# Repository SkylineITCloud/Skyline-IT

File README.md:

# Skyline IT

The official single-page website for **Skyline IT**, a South African holding company building brands across technology, Internet Of Things (IoT), electronics, fashion, and education.

The site presents the Skyline IT story, its portfolio companies, core values, industry focus, and contact information.

## Live site structure

```text
Skyline IT/
├── index.html       # Complete responsive website: markup, styles, and interactions
├── images/
│   └── Logo.png     # Skyline IT brand logo and favicon
└── README.md        # Project documentation
```

## Portfolio companies

- **Skyline IT & Cloud** — Digital services, web and mobile development, e-commerce, SEO, cloud hosting, and social media support.
- **Mzansi Connect** — Affordable Internet Of Things (IoT) products for South African homes, small businesses, utilities, and fleets.
- **Circuit Forge Technologies** — Electronics engineering, PCB design, embedded systems, firmware, and hardware prototyping.
- **VALOW.** — South African streetwear and community-led apparel.
- **StudySync** — A study-group management and real-time collaboration platform for students.

## Running the website

This project has no build step or package dependencies.

1. Open `index.html` in any modern web browser.
2. For the most reliable local testing experience, serve the folder with a local web server, then open the provided local address in a browser.

For example, if Python is installed:

```powershell
python -m http.server 8000
```

Then visit `http://localhost:8000`.

## Customising content

All site content, styling, and JavaScript are contained in `index.html`.

- Update company descriptions, services, or founder information directly in the relevant HTML sections.
- Update the contact email by replacing `projectpstg@gmail.com` in the page.
- Replace `images/Logo.png` to update the navigation, hero, footer, and browser favicon logo.
- The visual theme is controlled by the CSS variables near the top of `index.html`.

## Technologies

- HTML5
- CSS3, including responsive layouts and animations
- Vanilla JavaScript for navigation, scroll states, and reveal effects
- Google Fonts: Space Grotesk and JetBrains Mono

## Contact

For general enquiries or partnerships, email [projectpstg@gmail.com](mailto:projectpstg@gmail.com).

Based in Durban, South Africa.

## License

Copyright © 2025 Skyline IT. All rights reserved.

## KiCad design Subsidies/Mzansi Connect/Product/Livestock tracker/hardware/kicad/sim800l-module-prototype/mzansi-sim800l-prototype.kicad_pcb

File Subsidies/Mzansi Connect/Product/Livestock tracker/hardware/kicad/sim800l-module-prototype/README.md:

# SIM800L / NEO-6 / ESP32-C3 module prototype

**REVIEW-1 — 24 October 2026. Not released for fabrication or personal-safety use.** This is an electrically connected carrier reference for the user's selected SIM800L, NEO-6, ESP32-C3, USB-C TP4056 and lithium battery. It is separate from the preserved collar projects and supersedes the earlier component exploration.

## Open and inspect

Open `mzansi-sim800l-prototype.kicad_pro` in KiCad. The schematic contains actual electrical pins, wires and named nets, not a graphical block diagram. The PCB uses official KiCad stock footprints for carrier parts and connectors. External modules connect by **named wires**; their footprint, orientation, antenna area and mounting are not invented here. Two 15-pin MCU headers reproduce official pin numbering, but their placement is not a drop-in socket for the development board.

`generate_project.py` regenerates the electrical schematic, local symbol library, project settings, BOM and pin map. `build_layout.py` requires KiCad's bundled Python and regenerates the initial PCB placement; it does not preserve manual routing. Do not rerun it over a routed revision without saving that work. Generated source is mirrored to both GitHub folder copies.

## Connector contracts

| Carrier | Pins in order | Requirement |
|---|---|---|
| J6 SIM800L | 1 regulated 4.0V, 2 GND, 3 module RXD, 4 module TXD | Exactly four pins. Raw 2.8V UART is translated in both directions. Module must expose its own manual/onboard PWRKEY action; this interface cannot remotely press PWRKEY. A 5V-input SIM800L EVB is incompatible with this 4V contract without revision. |
| J8 NEO-6 | 1 regulated 3.3V, 2 GND, 3 module TXD, 4 module RXD | Exactly four pins. Select a board genuinely supporting a 3.3V supply and 3.3V UART; a breakout with a high-dropout onboard regulator may need a different connection. |
| J7 MCU | Official DevKitM-1 **J1 pins 1–15**, unchanged | The reference is explicitly Espressif ESP32-C3-DevKitM-1 / current N4X variant, not an unspecified SuperMini. |
| J11 MCU | Official DevKitM-1 **J3 pins 1–15**, unchanged | 30 physical header positions in total; this is not the bare ESP32 chip/module pad count. |
| J1 battery | Protected pack positive, protected pack negative | Single cell only, polarity verified. Never connect directly to raw cell pads behind pack protection. |
| J2 charger | TP4056 BAT+, BAT− | USB-C is on the external charger board. Charger must support the selected pack and the charge/run isolation described below. |
| J3 3.3V regulator | VIN, GND, VOUT | External Pololu S13V25F3, item 4980; verify actual wire names, not assumed physical pad order. |
| J4 modem regulator | VIN, GND, VOUT | External Pololu S18V20ALV, item 2572; preset and verify output at 4.0V before connecting modem. |
| J5 mode switch | 1 common, 2 CHARGE, 3 RUN | Harness assignment, not a claim that every switch's common is pin 1. External SPDT centre-off, break-before-make switch, rated for the full battery current. |
| J9 SOS | SOS input, GND | Normally open button; GPIO3 has an external 10k pull-up. |

### MCU assignments

SIM UART: GPIO7 TX → translator → SIM RX, and SIM TX → translator → GPIO6 RX. GPS UART: GPIO5 TX → GPS RX, GPS TX → GPIO4 RX. Firmware must explicitly remap the two hardware UARTs. GPIO1 controls UART output enable, with R5 100k pulling it off by default. GPIO20/21 remain unused because the official board's USB-UART bridge is attached there. GPIO18/19 USB and boot straps GPIO2/8/9 are also unused. GPIO10 drives the indicator through 1k; GPIO0 reads battery voltage through 200k/100k plus 100nF.

At 4.2V, ADC input is nominally 1.4V, approximately 1.419V with worst-case 1% divider tolerance. Select the ESP32-C3 ADC's **12dB attenuation** (legacy API names it 11dB), use calibration and allow about 35ms settling after power-up. Do not reuse the historical GPIO19 ADC assignment.

The historical collar firmware is **not compatible unchanged**. Its UART/pin assignments, automated PWRKEY handling, ADC configuration and message transport need revision for this carrier. No firmware build or flashing result is claimed. A personal-safety implementation must use authenticated device transport and the intended event protocol; legacy public livestock telemetry is not an acceptable substitute.

## Power and charging

J5 connects pack positive either to the charger's BAT+ or to RUN_BAT; it cannot connect both in a stable switch position. The device is off while charging. This implements a deliberately simple charge/run interlock because TP4056 has no system load-sharing output. Grounds stay common through the protected pack terminals. The external switch must be break-before-make; verify the harness with a continuity meter before connecting a cell.

Use only one MCU power method at a time. In this reference it is the regulated 3.3V header supply. Do not connect the development board's USB or 5V source simultaneously. Disconnect the carrier power harness for USB programming. A bypassing USB supply would defeat the intended off-while-charging behavior.

TXU0202DCUR provides opposite fixed directions for UART. VCCA uses 3.3V; VCCB uses a separate TLV75528PDBVR 2.8V rail. OE uses GPIO1 and defaults off through R5. Thus no inaccessible SIM VDD_EXT pad is assumed. U2 has 1µF input/output capacitors; U1 has 100nF on both supply domains. C2/C3 are local modem reservoir capacitors, to be fitted close to J6; the modem itself may need additional local capacitance at the remote end of its harness.

Keep GPIO1/OE low throughout boot, reset, programming and modem power transitions. Firmware must set OE low before configuring the TX output, and enable it only after the operator manually starts the modem and confirms its appropriate ready indication. Set OE low before manual modem shutdown or changing the power mode. The four-pin interface has no VDD_EXT/status signal, so it **cannot automatically detect the modem's internal power state**. A timed UART handshake alone does not remove that limitation. Unattended operation needs a verified power-state interlock or a revised interface; this controlled bench prototype does not claim one.

S18V20ALV's published 2A capability is typical near equal input/output voltage. It is **not a guarantee** of 2A at the lowest battery voltage. Measure at the modem, not only at the regulator. Require 3.4–4.4V through real transmit bursts. If the selected regulator fails that test, change the supply design before any field use. Avoid solderless breadboard power paths.

## Battery requirements

Specify a documented, independently protected **1S Li-ion/LiPo pack**, 3.7V nominal and **4.20V maximum charge**, initially at least **2000mAh**, rated at least **5A continuous** and **8A pulses** with a documented pulse duration and repetition limit covering measurements. Capacity alone does not establish current capability. This is a bench/prototype requirement, not a promise that the pack fits jewellery or delivers a particular runtime.

Use pack protection against overcharge, overdischarge and short circuit, appropriate pack temperature sensing, an appropriately rated fuse and correct connector polarity. Select fuse/time-current behavior against actual inrush and burst measurements; a fuse is not specified solely from its printed current. The external switch, pack wiring and J1/J3/J4/J5 connections must support at least the same 5A continuous/8A pulse path. The carrier's Phoenix MKDS 1,5 power terminal family has a manufacturer nominal rating of 17.5A; PCB copper and wire limits still require review.

Start charging at **no more than 500mA, or the pack manufacturer's lower limit**. Verify actual TP4056 variant, RPROG and measured current rather than assuming a generic resistor formula or the module's factory 1A setting. A grounded TEMP pin disables battery-temperature supervision: a charger board with that arrangement must be revised or replaced with a verified temperature-supervised implementation for the selected cell. A USB-C connector alone does not prove correct CC pull-downs; verify the charger board's USB-C implementation. Do not substitute LiFePO4, 4.35V high-voltage lithium or multiple cells for this pack specification.

At a conservative 3.0V pack and 80% conversion efficiency, a 4.0V/2A modem burst alone requires about 3.33A from the pack, before MCU/GPS consumption. Low-battery thresholds must shut the system down before the regulators leave their operating range, with hardware fault protection independent of firmware. Validate the selected pack's cutoff and regulator behavior; an arbitrary generic pack protector may trip below a regulator's minimum input. No seven-day runtime claim is made.

## Release gates

The PCB's routing state and actual native KiCad results are recorded in `VALIDATION.md`. No Gerbers or assembly order are released. Even a clean software rules check does not validate antenna placement, module authenticity, battery temperature behavior, cellular service or an emergency delivery path.

Before fabrication: approve exact external module variants and harnesses, verify mechanical placement and connector/current ratings, resolve any remaining routing/DRC issues, review copper/return-path current and temperature, and perform the measured power tests. Before wearer trials: verify operator 2G/GPRS availability in intended areas, authenticated device transport, pairing, replay resistance, consent and notification delivery. SIM800L is a 2G module; compatibility with future networks is not assumed.

## Primary sources

- [Espressif DevKitM-1 user guide: exact 15+15 header tables and mutually exclusive power methods](https://docs.espressif.com/projects/esp-dev-kits/en/latest/esp32c3/esp32-c3-devkitm-1/user_guide.html).
- [SIMCom SIM800H/SIM800L Hardware Design V2.02, manufacturer document hosted by Electrokit](https://www.electrokit.com/upload/product/41018/41018214/SIM800L-SIMCom.pdf).
- [u-blox NEO-6 data sheet](https://content.u-blox.com/sites/default/files/products/documents/NEO-6_DataSheet_%28GPS.G6-HW-09005%29.pdf).
- [Top Power TP4056 manufacturer data sheet](https://www.toppwr.com/uploadfile/file/20240307/65e993d6379ea.pdf).
- [TI TXU0202 data sheet](https://www.ti.com/lit/ds/symlink/txu0202.pdf) and [TI TLV755P data sheet](https://www.ti.com/lit/ds/symlink/tlv755p.pdf).
- [Pololu S13V25F3](https://www.pololu.com/product/4980) and [S18V20ALV](https://www.pololu.com/product/2572).
- [Phoenix Contact MKDS 1,5/2-5,08](https://www.phoenixcontact.com/en-us/products/printed-circuit-board-terminal-mkds-15-2-508-1715721).
- [Espressif ESP32-C3 ADC reference](https://docs.espressif.com/projects/esp-idf/en/v4.4.5/esp32c3/api-reference/peripherals/adc.html).

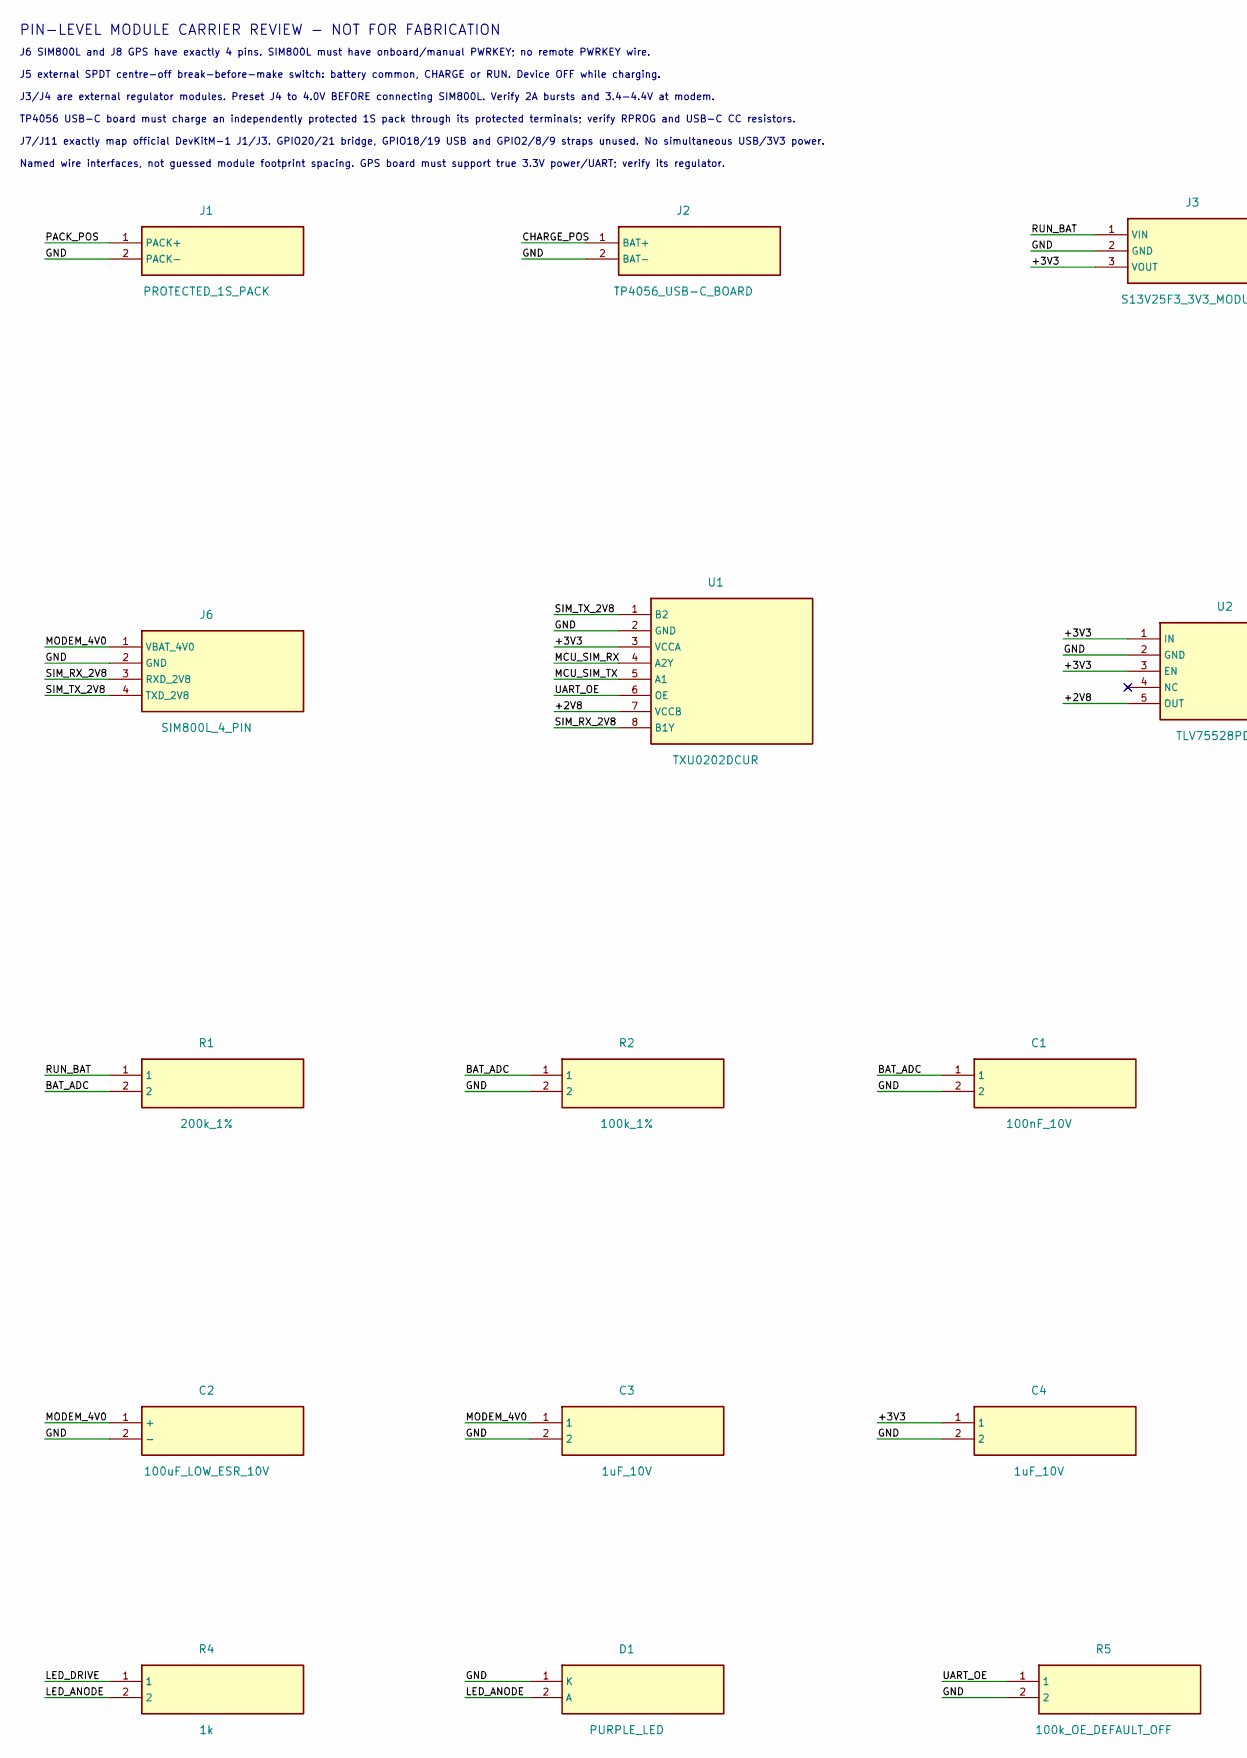
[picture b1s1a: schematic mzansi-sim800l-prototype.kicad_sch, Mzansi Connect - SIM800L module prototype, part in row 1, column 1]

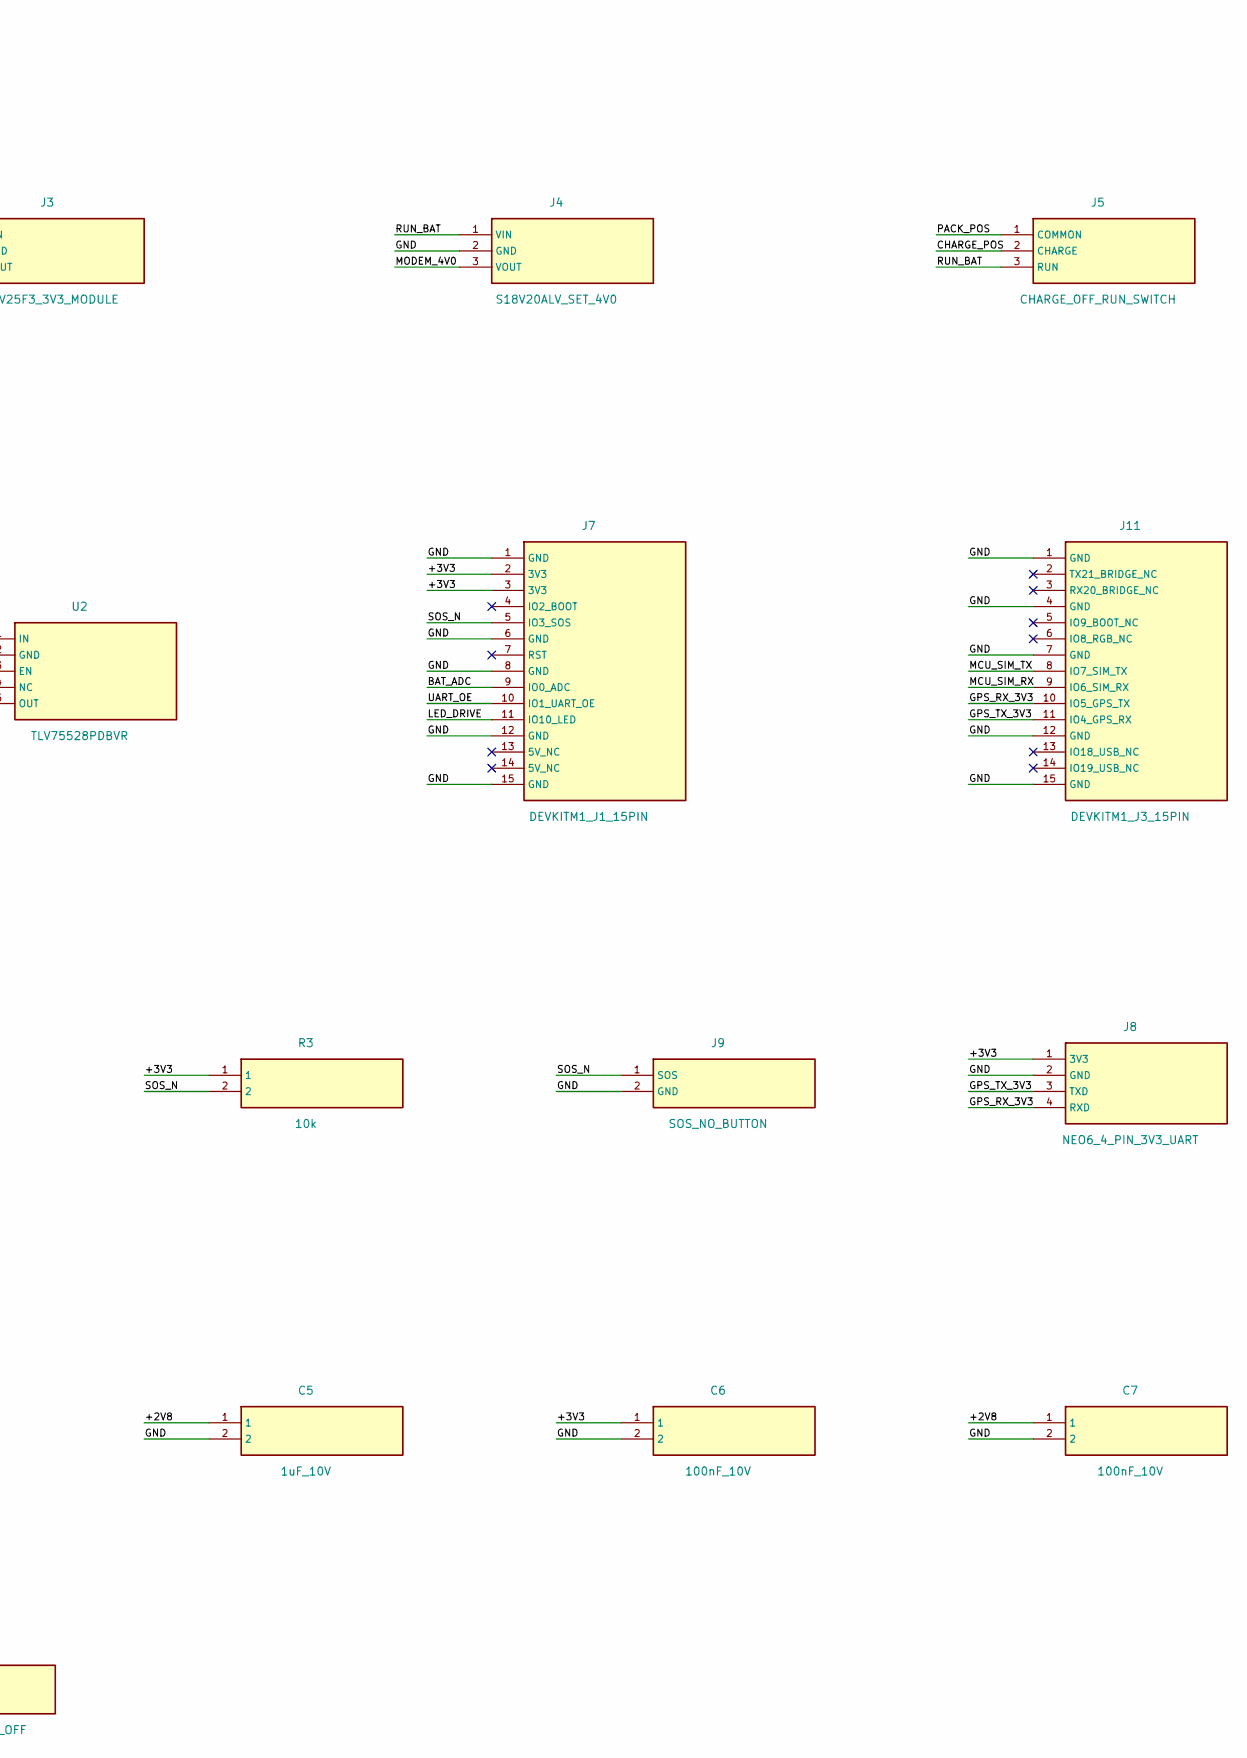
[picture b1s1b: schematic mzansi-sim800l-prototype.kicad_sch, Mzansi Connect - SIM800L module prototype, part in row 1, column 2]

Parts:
C1, C6, C7: 100nF_10V; C_0603_1608Metric
C2: 100uF_LOW_ESR_10V; CP_Elec_6.3x5.8
C3, C4, C5: 1uF_10V; C_0603_1608Metric
D1: PURPLE_LED; LED_0603_1608Metric
J1: PROTECTED_1S_PACK; TerminalBlock_Phoenix_MKDS-1,5-2-5.08_1x02_P5.08mm_Horizont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
J2: TP4056_USB-C_BOARD; TerminalBlock_Phoenix_MKDS-1,5-2-5.08_1x02_P5.08mm_Horizont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
J3: S13V25F3_3V3_MODULE; TerminalBlock_Phoenix_MKDS-1,5-3-5.08_1x03_P5.08mm_Horizont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
J4: S18V20ALV_SET_4V0; TerminalBlock_Phoenix_MKDS-1,5-3-5.08_1x03_P5.08mm_Horizont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
J5: CHARGE_OFF_RUN_SWITCH; TerminalBlock_Phoenix_MKDS-1,5-3-5.08_1x03_P5.08mm_Horizont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
J6: SIM800L_4_PIN; PinHeader_1x04_P2.54mm_Vertical
J7: DEVKITM1_J1_15PIN; PinHeader_1x15_P2.54mm_Vertical
J8: NEO6_4_PIN_3V3_UART; PinHeader_1x04_P2.54mm_Vertical
J9: SOS_NO_BUTTON; PinHeader_1x02_P2.54mm_Vertical
J11: DEVKITM1_J3_15PIN; PinHeader_1x15_P2.54mm_Vertical
R1: 200k_1%; R_0603_1608Metric
R2: 100k_1%; R_0603_1608Metric
R3: 10k; R_0603_1608Metric
R4: 1k; R_0603_1608Metric
R5: 100k_OE_DEFAULT_OFF; R_0603_1608Metric
U1: TXU0202DCUR; VSSOP-8_2.3x2mm_P0.5mm
U2: TLV75528PDBVR; SOT-23-5

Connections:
/+2V8: C5.1, C7.1, U1.7 (VCCB), U2.5 (OUT)
/+3V3: C4.1, C6.1, J3.3 (VOUT), J7.2 (3V3), J7.3 (3V3), J8.1 (3V3), R3.1, U1.3 (VCCA), U2.1 (IN), U2.3 (EN)
/BAT_ADC: C1.1, J7.9 (IO0_ADC), R1.2, R2.1
/CHARGE_POS: J2.1 (BAT+), J5.2 (CHARGE)
/GND: C1.2, C2.2 (-), C3.2, C4.2, C5.2, C6.2, C7.2, D1.1 (K), J1.2 (PACK-), J2.2 (BAT-), J3.2 (GND), J4.2 (GND), J6.2 (GND), J7.1 (GND), J7.6 (GND), J7.8 (GND), J7.12 (GND), J7.15 (GND), J8.2 (GND), J9.2 (GND), J11.1 (GND), J11.4 (GND), J11.7 (GND), J11.12 (GND), J11.15 (GND), R2.2, R5.2, U1.2 (GND), U2.2 (GND)
/GPS_RX_3V3: J8.4 (RXD), J11.10 (IO5_GPS_TX)
/GPS_TX_3V3: J8.3 (TXD), J11.11 (IO4_GPS_RX)
/LED_ANODE: D1.2 (A), R4.2
/LED_DRIVE: J7.11 (IO10_LED), R4.1
/MCU_SIM_RX: J11.9 (IO6_SIM_RX), U1.4 (A2Y)
/MCU_SIM_TX: J11.8 (IO7_SIM_TX), U1.5 (A1)
/MODEM_4V0: C2.1 (+), C3.1, J4.3 (VOUT), J6.1 (VBAT_4V0)
/PACK_POS: J1.1 (PACK+), J5.1 (COMMON)
/RUN_BAT: J3.1 (VIN), J4.1 (VIN), J5.3 (RUN), R1.1
/SIM_RX_2V8: J6.3 (RXD_2V8), U1.8 (B1Y)
/SIM_TX_2V8: J6.4 (TXD_2V8), U1.1 (B2)
/SOS_N: J7.5 (IO3_SOS), J9.1 (SOS), R3.2
/UART_OE: J7.10 (IO1_UART_OE), R5.1, U1.6 (OE)

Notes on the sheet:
PIN-LEVEL MODULE CARRIER REVIEW - NOT FOR FABRICATION
J6 SIM800L and J8 GPS have exactly 4 pins. SIM800L must have onboard/manual PWRKEY; no remote PWRKEY wire.
J5 external SPDT centre-off break-before-make switch: battery common, CHARGE or RUN. Device OFF while charging.
J3/J4 are external regulator modules. Preset J4 to 4.0V BEFORE connecting SIM800L. Verify 2A bursts and 3.4-4.4V at modem.
TP4056 USB-C board must charge an independently protected 1S pack through its protected terminals; verify RPROG and USB-C CC resistors.
J7/J11 exactly map official DevKitM-1 J1/J3. GPIO20/21 bridge, GPIO18/19 USB and GPIO2/8/9 straps unused. No simultaneous USB/3V3 power.
Named wire interfaces, not guessed module footprint spacing. GPS board must support true 3.3V power/UART; verify its regulator.

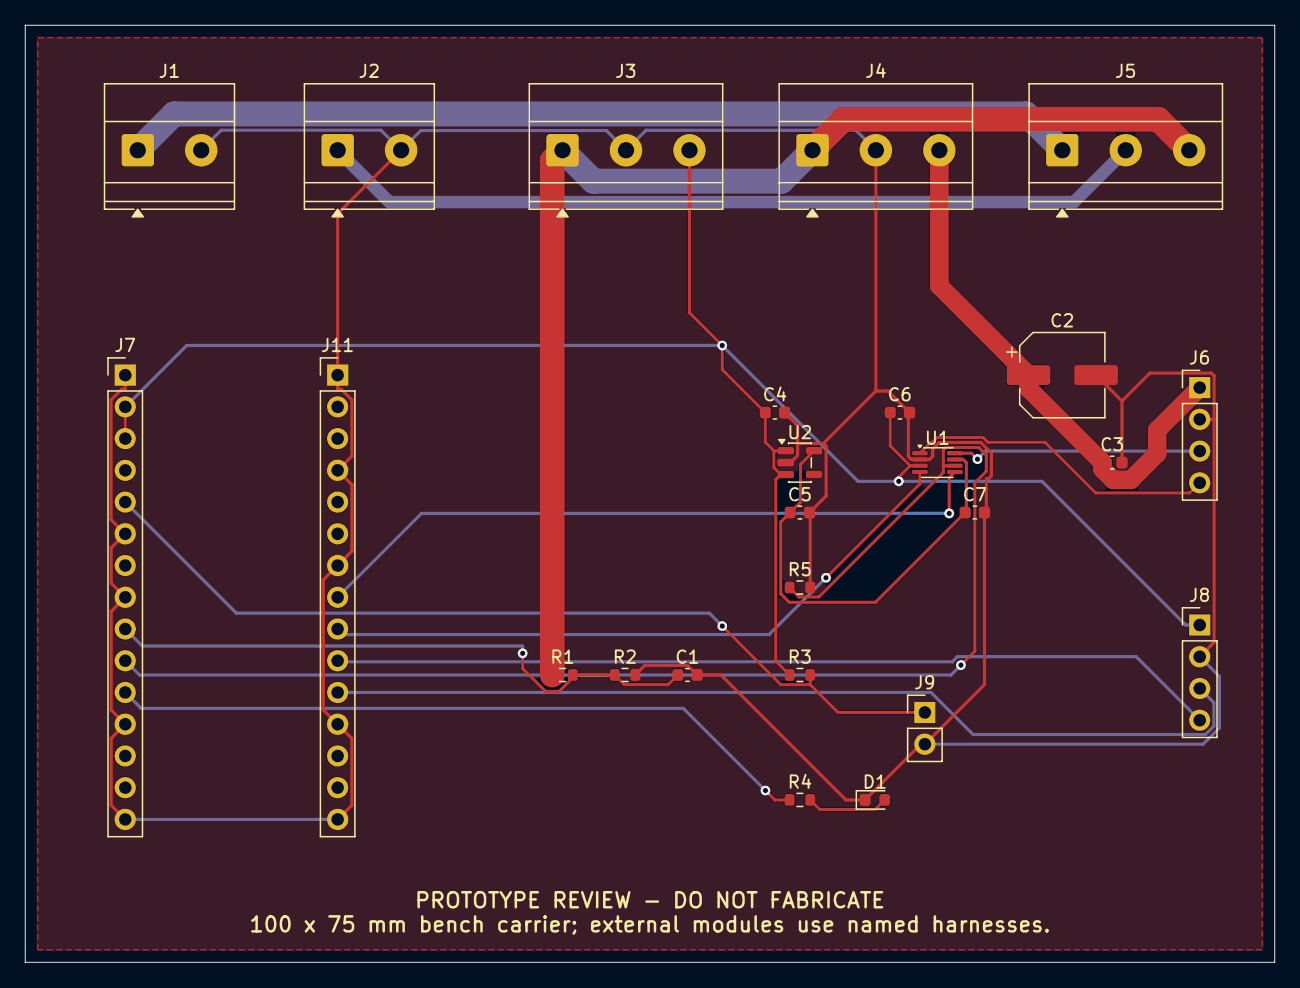
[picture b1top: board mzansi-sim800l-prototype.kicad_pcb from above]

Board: 2 copper layers, 100.0 x 75.0 mm, 25 parts (0 on the bottom side), 18 nets.

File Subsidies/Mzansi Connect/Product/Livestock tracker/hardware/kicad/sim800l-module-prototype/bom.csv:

Reference,Value_or_interface,Footprint,Datasheet
J1,PROTECTED_1S_PACK,"TerminalBlock_Phoenix:TerminalBlock_Phoenix_MKDS-1,5-2-5.08_1x02_P5.08mm_Horizontal",
J2,TP4056_USB-C_BOARD,"TerminalBlock_Phoenix:TerminalBlock_Phoenix_MKDS-1,5-2-5.08_1x02_P5.08mm_Horizontal",
J3,S13V25F3_3V3_MODULE,"TerminalBlock_Phoenix:TerminalBlock_Phoenix_MKDS-1,5-3-5.08_1x03_P5.08mm_Horizontal",
J4,S18V20ALV_SET_4V0,"TerminalBlock_Phoenix:TerminalBlock_Phoenix_MKDS-1,5-3-5.08_1x03_P5.08mm_Horizontal",
J5,CHARGE_OFF_RUN_SWITCH,"TerminalBlock_Phoenix:TerminalBlock_Phoenix_MKDS-1,5-3-5.08_1x03_P5.08mm_Horizontal",
J6,SIM800L_4_PIN,Connector_PinHeader_2.54mm:PinHeader_1x04_P2.54mm_Vertical,
U1,TXU0202DCUR,Package_SO:VSSOP-8_2.3x2mm_P0.5mm,https://www.ti.com/lit/ds/symlink/txu0202.pdf
U2,TLV75528PDBVR,Package_TO_SOT_SMD:SOT-23-5,https://www.ti.com/lit/ds/symlink/tlv755p.pdf
J7,DEVKITM1_J1_15PIN,Connector_PinHeader_2.54mm:PinHeader_1x15_P2.54mm_Vertical,
J11,DEVKITM1_J3_15PIN,Connector_PinHeader_2.54mm:PinHeader_1x15_P2.54mm_Vertical,
J8,NEO6_4_PIN_3V3_UART,Connector_PinHeader_2.54mm:PinHeader_1x04_P2.54mm_Vertical,
R1,200k_1%,Resistor_SMD:R_0603_1608Metric,
R2,100k_1%,Resistor_SMD:R_0603_1608Metric,
C1,100nF_10V,Capacitor_SMD:C_0603_1608Metric,
R3,10k,Resistor_SMD:R_0603_1608Metric,
J9,SOS_NO_BUTTON,Connector_PinHeader_2.54mm:PinHeader_1x02_P2.54mm_Vertical,
C2,100uF_LOW_ESR_10V,Capacitor_SMD:CP_Elec_6.3x5.8,
C3,1uF_10V,Capacitor_SMD:C_0603_1608Metric,
C4,1uF_10V,Capacitor_SMD:C_0603_1608Metric,
C5,1uF_10V,Capacitor_SMD:C_0603_1608Metric,
C6,100nF_10V,Capacitor_SMD:C_0603_1608Metric,
C7,100nF_10V,Capacitor_SMD:C_0603_1608Metric,
R4,1k,Resistor_SMD:R_0603_1608Metric,
D1,PURPLE_LED,LED_SMD:LED_0603_1608Metric,
R5,100k_OE_DEFAULT_OFF,Resistor_SMD:R_0603_1608Metric,

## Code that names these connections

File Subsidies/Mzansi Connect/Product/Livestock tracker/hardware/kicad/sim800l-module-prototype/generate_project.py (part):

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conn('J3', 'S13V25F3_3V3_MODULE', ['VIN', 'GND', 'VOUT'], ['RUN_BAT', 'GND', '+3V3'], 200, 50, ['passive', 'passive', 'power_out'])
conn('J4', 'S18V20ALV_SET_4V0', ['VIN', 'GND', 'VOUT'], ['RUN_BAT', 'GND', 'MODEM_4V0'], 280, 50, ['passive', 'passive', 'power_out'])
conn('J5', 'CHARGE_OFF_RUN_SWITCH', ['COMMON', 'CHARGE', 'RUN'], ['PACK_POS', 'CHARGE_POS', 'RUN_BAT'], 365, 50)
conn('J6', 'SIM800L_4_PIN', ['VBAT_4V0', 'GND', 'RXD_2V8', 'TXD_2V8'], ['MODEM_4V0', 'GND', 'SIM_RX_2V8', 'SIM_TX_2V8'], 45, 115, ['power_in', 'passive', 'input', 'output'])
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symbol('U2', 'TLV75528PDBVR', [('1', 'IN', 'power_in'), ('2', 'GND', 'power_in'), ('3', 'EN', 'input'), ('4', 'NC', 'no_connect'), ('5', 'OUT', 'power_out')], ['+3V3', 'GND', '+3V3', None, '+2V8'], 205, 115, 'Package_TO_SOT_SMD:SOT-23-5', 'https://www.ti.com/lit/ds/symlink/tlv755p.pdf')
conn('J7', 'DEVKITM1_J1_15PIN', ['GND', '3V3', '3V3', 'IO2_BOOT', 'IO3_SOS', 'GND', 'RST', 'GND', 'IO0_ADC', 'IO1_UART_OE', 'IO10_LED', 'GND', '5V_NC', '5V_NC', 'GND'], ['GND', '+3V3', '+3V3', None, 'SOS_N', 'GND', None, 'GND', 'BAT_ADC', 'UART_OE', 'LED_DRIVE', 'GND', None, None, 'GND'], 285, 115)
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conn('J8', 'NEO6_4_PIN_3V3_UART', ['3V3', 'GND', 'TXD', 'RXD'], ['+3V3', 'GND', 'GPS_TX_3V3', 'GPS_RX_3V3'], 370, 180, ['power_in', 'passive', 'output', 'input'])
rfp = 'Resistor_SMD:R_0603_1608Metric'
cfp = 'Capacitor_SMD:C_0603_1608Metric'
passive('R1', '200k_1%', ['RUN_BAT', 'BAT_ADC'], 45, 180, rfp)
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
